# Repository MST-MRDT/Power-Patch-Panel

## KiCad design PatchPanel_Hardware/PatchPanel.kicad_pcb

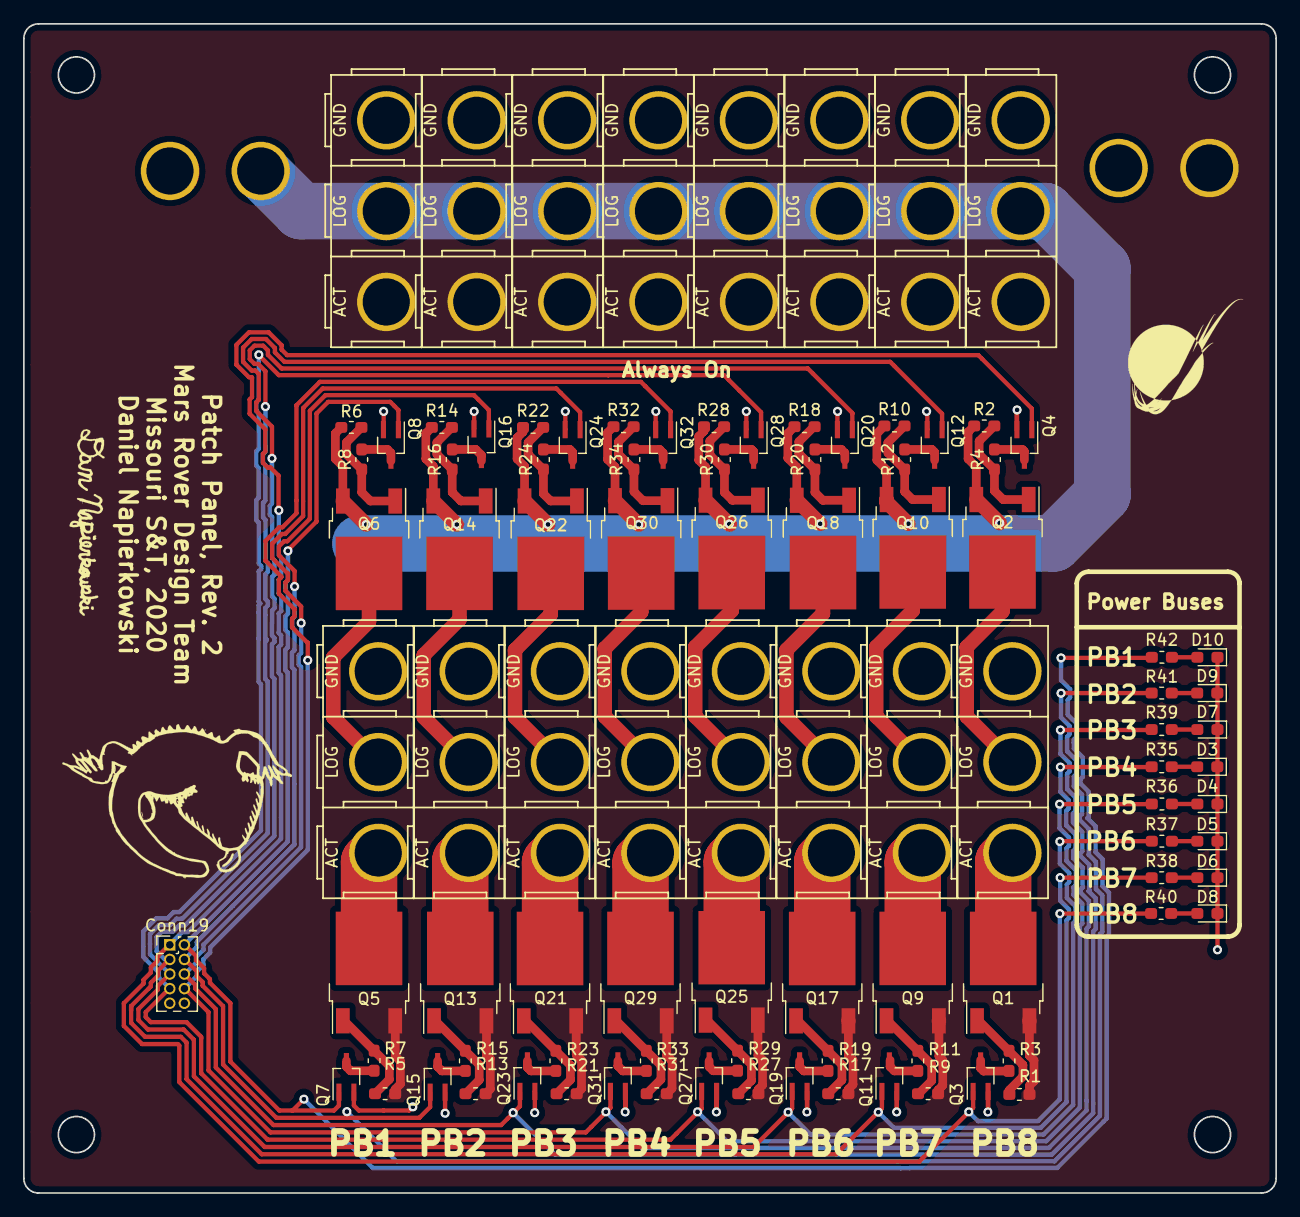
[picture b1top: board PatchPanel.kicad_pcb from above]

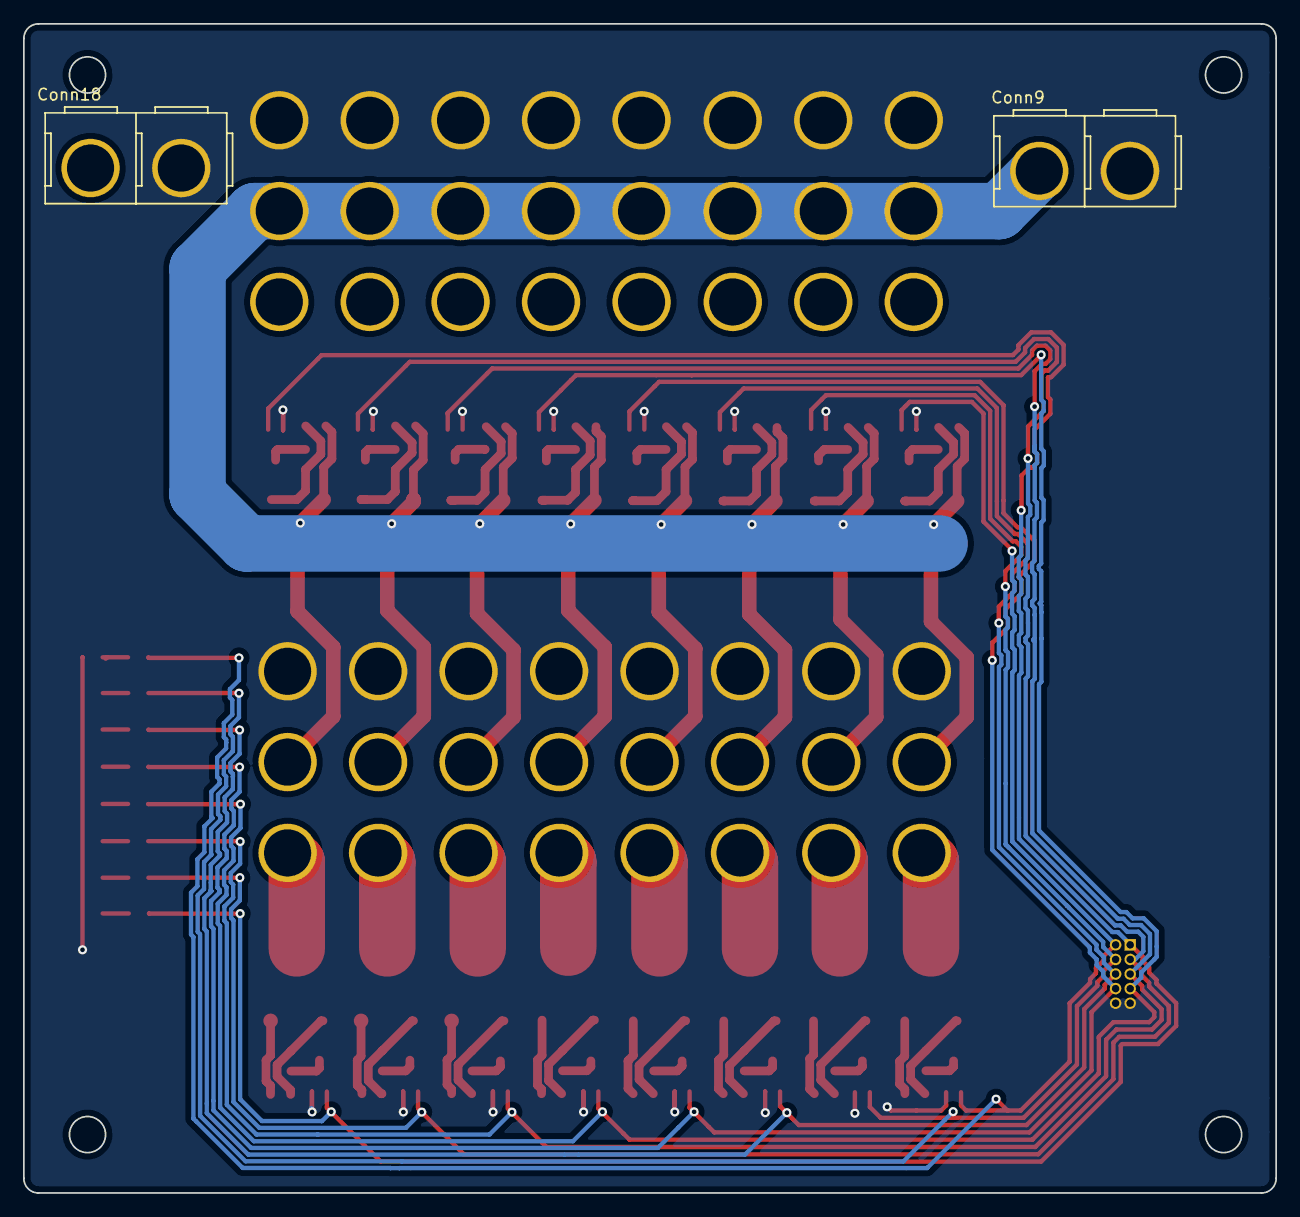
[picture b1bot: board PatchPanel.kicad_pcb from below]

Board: 2 copper layers, 109.0 x 101.7 mm, 99 parts (2 on the bottom side), 67 nets.

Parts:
Conn1, Conn2, Conn3, Conn4, Conn5, Conn6, Conn7, Conn8, Conn10, Conn11, Conn12, Conn13, Conn14, Conn15, Conn16, Conn17: AndersonPP; Anderson_3_Vertical_Side_by_Side
Conn9, Conn18: AndersonPP; Anderson_2_Vertical_Sidy_by_Side
Conn19: Molex_SL_10; PinHeader_2x05_P1.27mm_Vertical
D3, D4, D5, D6, D7, D8, D9, D10: OrangeLED; LED_0603_1608Metric_Pad1.05x0.95mm_HandSolder
Q1, Q2, Q5, Q6, Q9, Q10, Q13, Q14, Q17, Q18, Q21, Q22, Q25, Q26, Q29, Q30: Q_PMOS_GDS; TO-252-2
Q3, Q4, Q7, Q8, Q11, Q12, Q15, Q16, Q19, Q20, Q23, Q24, Q27, Q28, Q31, Q32: Q_NMOS_GSD; SOT-323_SC-70_Handsoldering
R1, R2, R3, R4, R5, R6, R7, R8, R9, R10, R11, R12, R13, R14, R15, R16, R17, R18, R19, R20, R21, R22, R23, R24, R27, R28, R29, R30, R31, R32, R33, R34: 22k; R_0603_1608Metric_Pad1.05x0.95mm_HandSolder
R35, R36, R37, R38, R39, R40, R41, R42: 300; R_0603_1608Metric_Pad1.05x0.95mm_HandSolder

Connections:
/Vact: Conn10.3, Conn11.3, Conn12.3, Conn13.3, Conn14.3, Conn15.3, Conn16.3, Conn17.3, Conn18.2, Q1.3, Q5.3, Q9.3, Q13.3, Q17.3, Q21.3, Q25.3, Q29.3, R1.2, R5.2, R9.2, R13.2, R17.2, R21.2, R27.2, R31.2
/Vlog: Conn9.2, Conn10.2, Conn11.2, Conn12.2, Conn13.2, Conn14.2, Conn15.2, Conn16.2, Conn17.2, Q2.3, Q6.3, Q10.3, Q14.3, Q18.3, Q22.3, Q26.3, Q30.3, R2.2, R6.2, R10.2, R14.2, R18.2, R22.2, R28.2, R32.2
GND: Conn1.1, Conn2.1, Conn3.1, Conn4.1, Conn5.1, Conn6.1, Conn7.1, Conn8.1, Conn9.1, Conn10.1, Conn11.1, Conn12.1, Conn13.1, Conn14.1, Conn15.1, Conn16.1, Conn17.1, Conn18.1, Conn19.9, Conn19.10, D3.1, D4.1, D5.1, D6.1, D7.1, D8.1, D9.1, D10.1, Q3.2, Q4.2, Q7.2, Q8.2, Q11.2, Q12.2, Q15.2, Q16.2, Q19.2, Q20.2, Q23.2, Q24.2, Q27.2, Q28.2, Q31.2, Q32.2
unnamed: Conn1.2, Q2.2
unnamed: Conn1.3, Q1.2
unnamed: Conn2.2, Q6.2
unnamed: Conn2.3, Q5.2
unnamed: Conn3.2, Q10.2
unnamed: Conn3.3, Q9.2
unnamed: Conn4.2, Q14.2
unnamed: Conn4.3, Q13.2
unnamed: Conn5.2, Q18.2
unnamed: Conn5.3, Q17.2
unnamed: Conn6.2, Q22.2
unnamed: Conn6.3, Q21.2
unnamed: Conn7.2, Q26.2
unnamed: Conn7.3, Q25.2
unnamed: Conn8.2, Q30.2
unnamed: Conn8.3, Q29.2
unnamed: D3.2, R35.2
unnamed: D4.2, R36.2
unnamed: D5.2, R37.2
unnamed: D6.2, R38.2
unnamed: D7.2, R39.2
unnamed: D8.2, R40.2
unnamed: D9.2, R41.2
unnamed: D10.2, R42.2
unnamed: Q1.1, R1.1, R3.2
unnamed: Q2.1, R2.1, R4.2
unnamed: Q3.3, R3.1
unnamed: Q4.3, R4.1
unnamed: Q5.1, R5.1, R7.2
unnamed: Q6.1, R6.1, R8.2
unnamed: Q7.3, R7.1
unnamed: Q8.3, R8.1
unnamed: Q9.1, R9.1, R11.2
unnamed: Q10.1, R10.1, R12.2
unnamed: Q11.3, R11.1
unnamed: Q12.3, R12.1
unnamed: Q13.1, R13.1, R15.2
unnamed: Q14.1, R14.1, R16.2
unnamed: Q15.3, R15.1
unnamed: Q16.3, R16.1
unnamed: Q17.1, R17.1, R19.2
unnamed: Q18.1, R18.1, R20.2
unnamed: Q19.3, R19.1
unnamed: Q20.3, R20.1
unnamed: Q21.1, R21.1, R23.2
unnamed: Q22.1, R22.1, R24.2
unnamed: Q23.3, R23.1
unnamed: Q24.3, R24.1
unnamed: Q25.1, R27.1, R29.2
unnamed: Q26.1, R28.1, R30.2
unnamed: Q27.3, R29.1
unnamed: Q28.3, R30.1
unnamed: Q29.1, R31.1, R33.2
unnamed: Q30.1, R32.1, R34.2
unnamed: Q31.3, R33.1
unnamed: Q32.3, R34.1
PB1: Conn19.2, Q7.1, Q8.1, R42.1
PB2: Conn19.4, Q15.1, Q16.1, R41.1
PB3: Conn19.6, Q23.1, Q24.1, R39.1
PB4: Conn19.8, Q31.1, Q32.1, R35.1
PB5: Conn19.7, Q27.1, Q28.1, R36.1
PB6: Conn19.5, Q19.1, Q20.1, R37.1
PB7: Conn19.3, Q11.1, Q12.1, R38.1
PB8: Conn19.1, Q3.1, Q4.1, R40.1

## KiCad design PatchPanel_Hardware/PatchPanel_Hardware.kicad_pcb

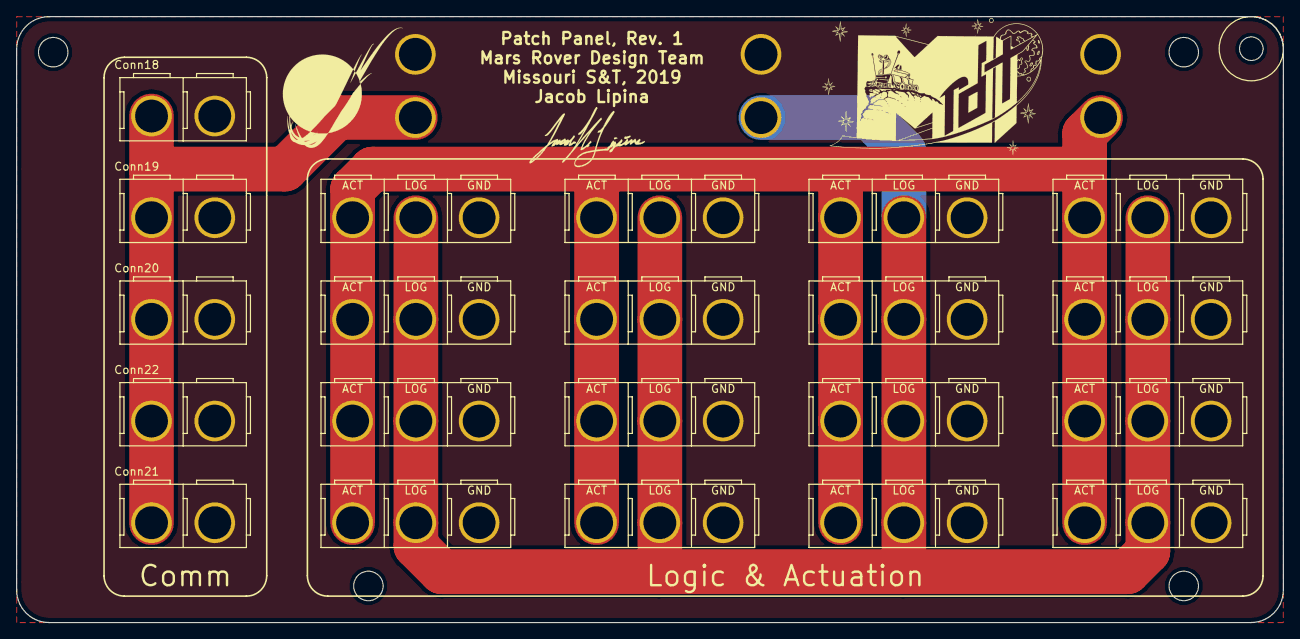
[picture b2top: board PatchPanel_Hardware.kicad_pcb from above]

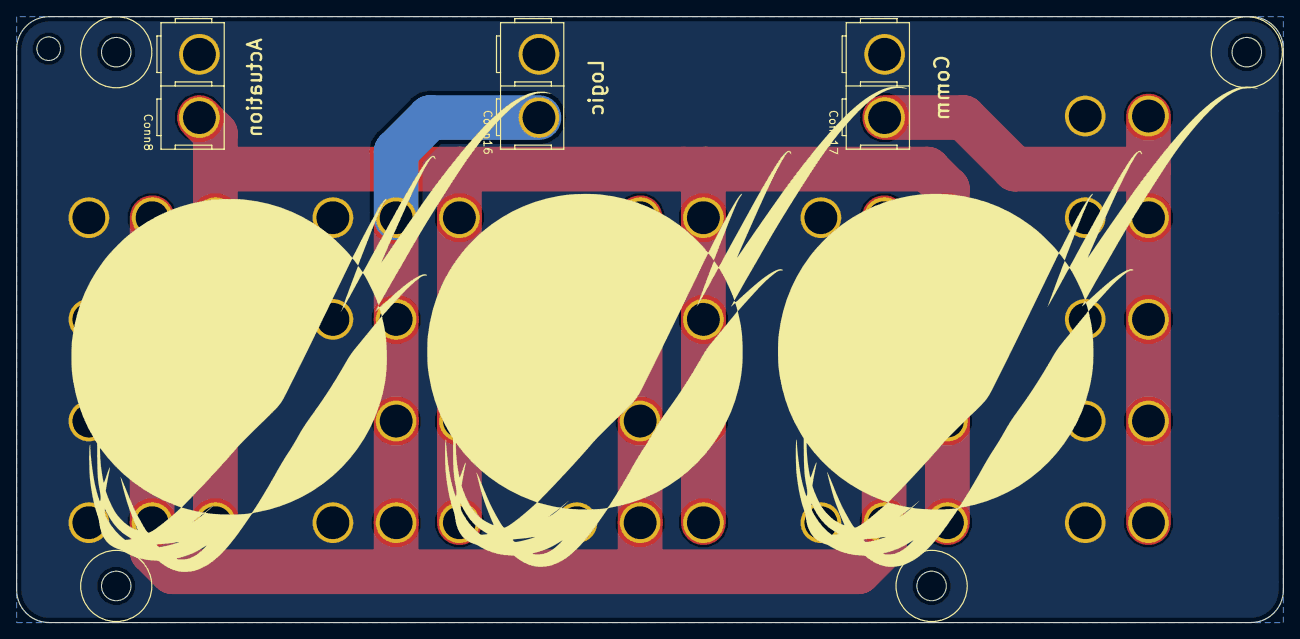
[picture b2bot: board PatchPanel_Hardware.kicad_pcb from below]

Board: 2 copper layers, 158.2 x 75.7 mm, 24 parts (3 on the bottom side), 4 nets.

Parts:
Conn1, Conn2, Conn3, Conn4, Conn5, Conn6, Conn7, Conn9, Conn10, Conn11, Conn12, Conn13, Conn14, Conn15, Conn23, Conn24: AndersonPP; Anderson_3_Vertical_Side_by_Side
Conn8, Conn16, Conn17, Conn18, Conn19, Conn20, Conn21, Conn22: AndersonPP; Anderson_2_Vertical_Sidy_by_Side

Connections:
+12C: Conn17.2, Conn18.2, Conn19.2, Conn20.2, Conn21.2, Conn22.2
+12L: Conn1.2, Conn2.2, Conn3.2, Conn4.2, Conn5.2, Conn6.2, Conn7.2, Conn9.2, Conn10.2, Conn11.2, Conn12.2, Conn13.2, Conn14.2, Conn15.2, Conn16.2, Conn23.2, Conn24.2
+12VA: Conn1.3, Conn2.3, Conn3.3, Conn4.3, Conn5.3, Conn6.3, Conn7.3, Conn8.2, Conn9.3, Conn10.3, Conn11.3, Conn12.3, Conn13.3, Conn14.3, Conn15.3, Conn23.3, Conn24.3
GND: Conn1.1, Conn2.1, Conn3.1, Conn4.1, Conn5.1, Conn6.1, Conn7.1, Conn8.1, Conn9.1, Conn10.1, Conn11.1, Conn12.1, Conn13.1, Conn14.1, Conn15.1, Conn16.1, Conn17.1, Conn18.1, Conn19.1, Conn20.1, Conn21.1, Conn22.1, Conn23.1, Conn24.1

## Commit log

2015-11-01 Create patch panel V1
2015-11-01 Added BOM
2015-11-17 Remove unnecessary backup files
2015-11-17 Update gitignore
2015-12-02 Removed 2-pin Connectors and RJ45 Pass-Through
2016-01-13 added moco power patch-thru, rearr 3-pin, gen dx
2016-01-13 Revert "added moco power patch-thru, rearr 3-pin, gen dx"
    This reverts commit e393c53abb352ea2a1f007c95e73af8e49a976a5.
2016-01-13 un-deleted brd file and re-added dxf
2016-01-13 imported new mlx connectors
2016-01-15 totally re-made patch panel, gen dxf
2016-01-15 added missing route
2016-01-16 Added ethernet hole
2016-01-19 added cutout, rerouted w/ vert app connectors for power in
2016-01-19 added rj45 standoff - needs placed
2016-01-21 github sucks. i changed some stuff
2016-01-22 FINAL PATCH PANEL REV 1
2016-11-06 2017 Patch Panel
    This patch panel for 2017 has 4 connections for the Logic bus, 6
    connections for the Logic & Actuation bus, 4 connections for the
    Actuation bus, and 2 connections for an extra bus.
2016-11-08 Last edits before fabrication
    tidied a couple traces and labels, and added a martian.
2017-11-08 2018 Patch Panel Rev1
    The 12V buses are being passed to patch panel. In order from bottom of power board to top, Actuation 15A, Logic 5A, Communication 5A. There is no extra bus this year. Add one more Logic/Act connection
2017-11-09 Font changed to vector
2018-03-15 Patch Panel Rev 2
    Eliminates all exclusive logic buses and added seven more actuation/logic combo buses. Added one more comm bus
2018-03-25 Rev.3 to Change Mounting Hole Locations
    Mounting holes on Rev.2 are incorrect because power board's size changed slightly and we only realized the holes didnt match up after we ordered Rev.2
2018-03-26 Adjusted bottom anderson positions
2018-03-26 Added gitignore and fixed silkscreen
2018-12-07 Created project and completed schematic
2018-12-13 Added Packages to Library
2018-12-13 Symbols named and packages assigned
2018-12-13 Outline and Hole Placement Complete
2018-12-13 Placed Double Andersons
2018-12-14 Placed Connectors & Routed Traces
2018-12-14 Added Silkscreen
2018-12-14 Created BOM
2018-12-31 Created Gerbs
2019-01-17 update rev 2 library
2019-10-08 layout
2019-10-10 board
2019-10-10 finished PCBdesign
2019-10-10 ready for PDR
2019-10-31 ready for board review
2019-11-18 add input label
2019-11-21 final change
2019-11-21 before review
2019-11-26 fixed board review issue
2019-12-06 matching
2019-12-11 change molex
2019-12-11 add LED to anderson
2019-12-11 BoardReview
2019-12-11 add gerbs
2019-12-14 bom.scv
2019-12-15 fix bom file
2020-01-21 Created Step File
2020-03-06 Redid entire schematic to be more organized and compact
2020-03-06 added some silks, generated Gerbs
